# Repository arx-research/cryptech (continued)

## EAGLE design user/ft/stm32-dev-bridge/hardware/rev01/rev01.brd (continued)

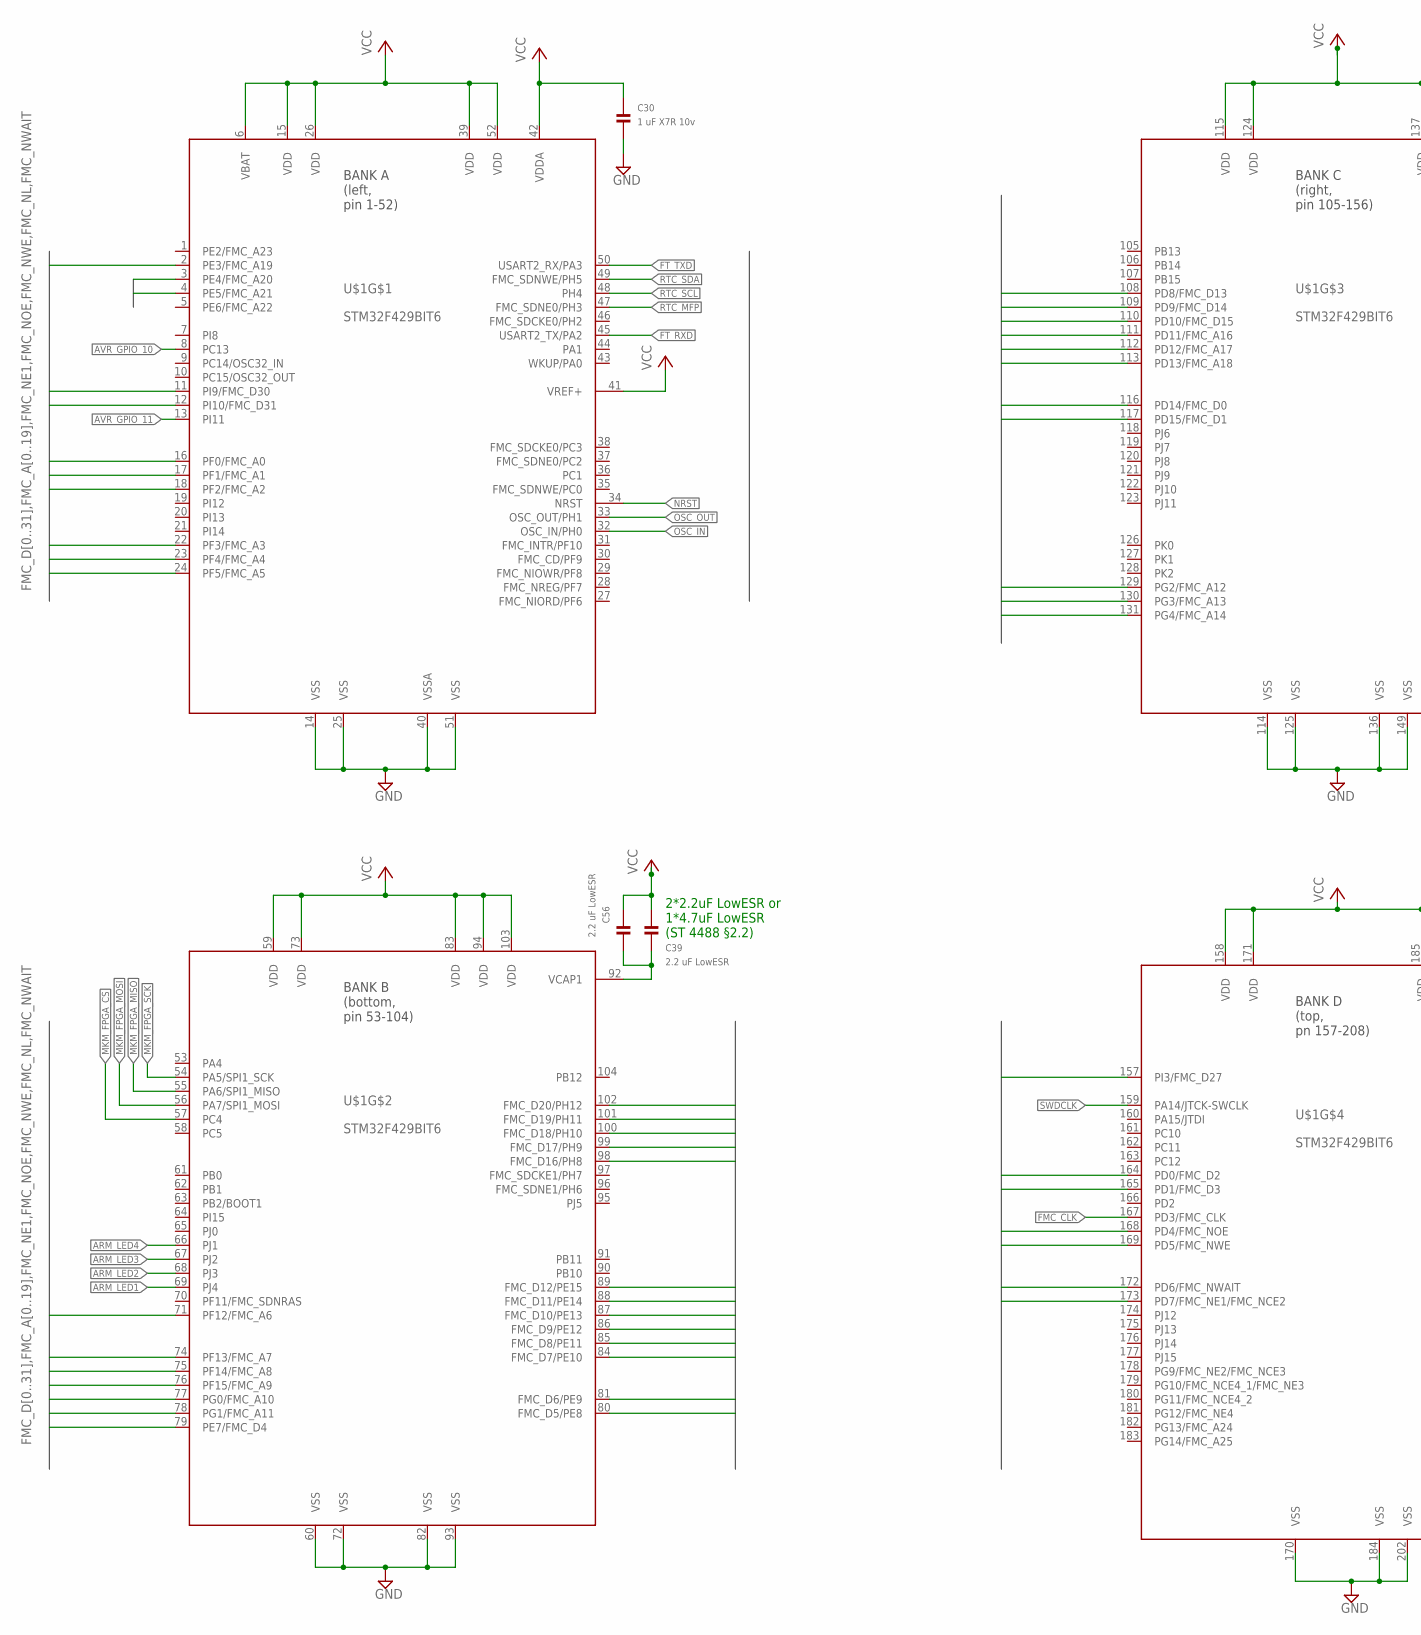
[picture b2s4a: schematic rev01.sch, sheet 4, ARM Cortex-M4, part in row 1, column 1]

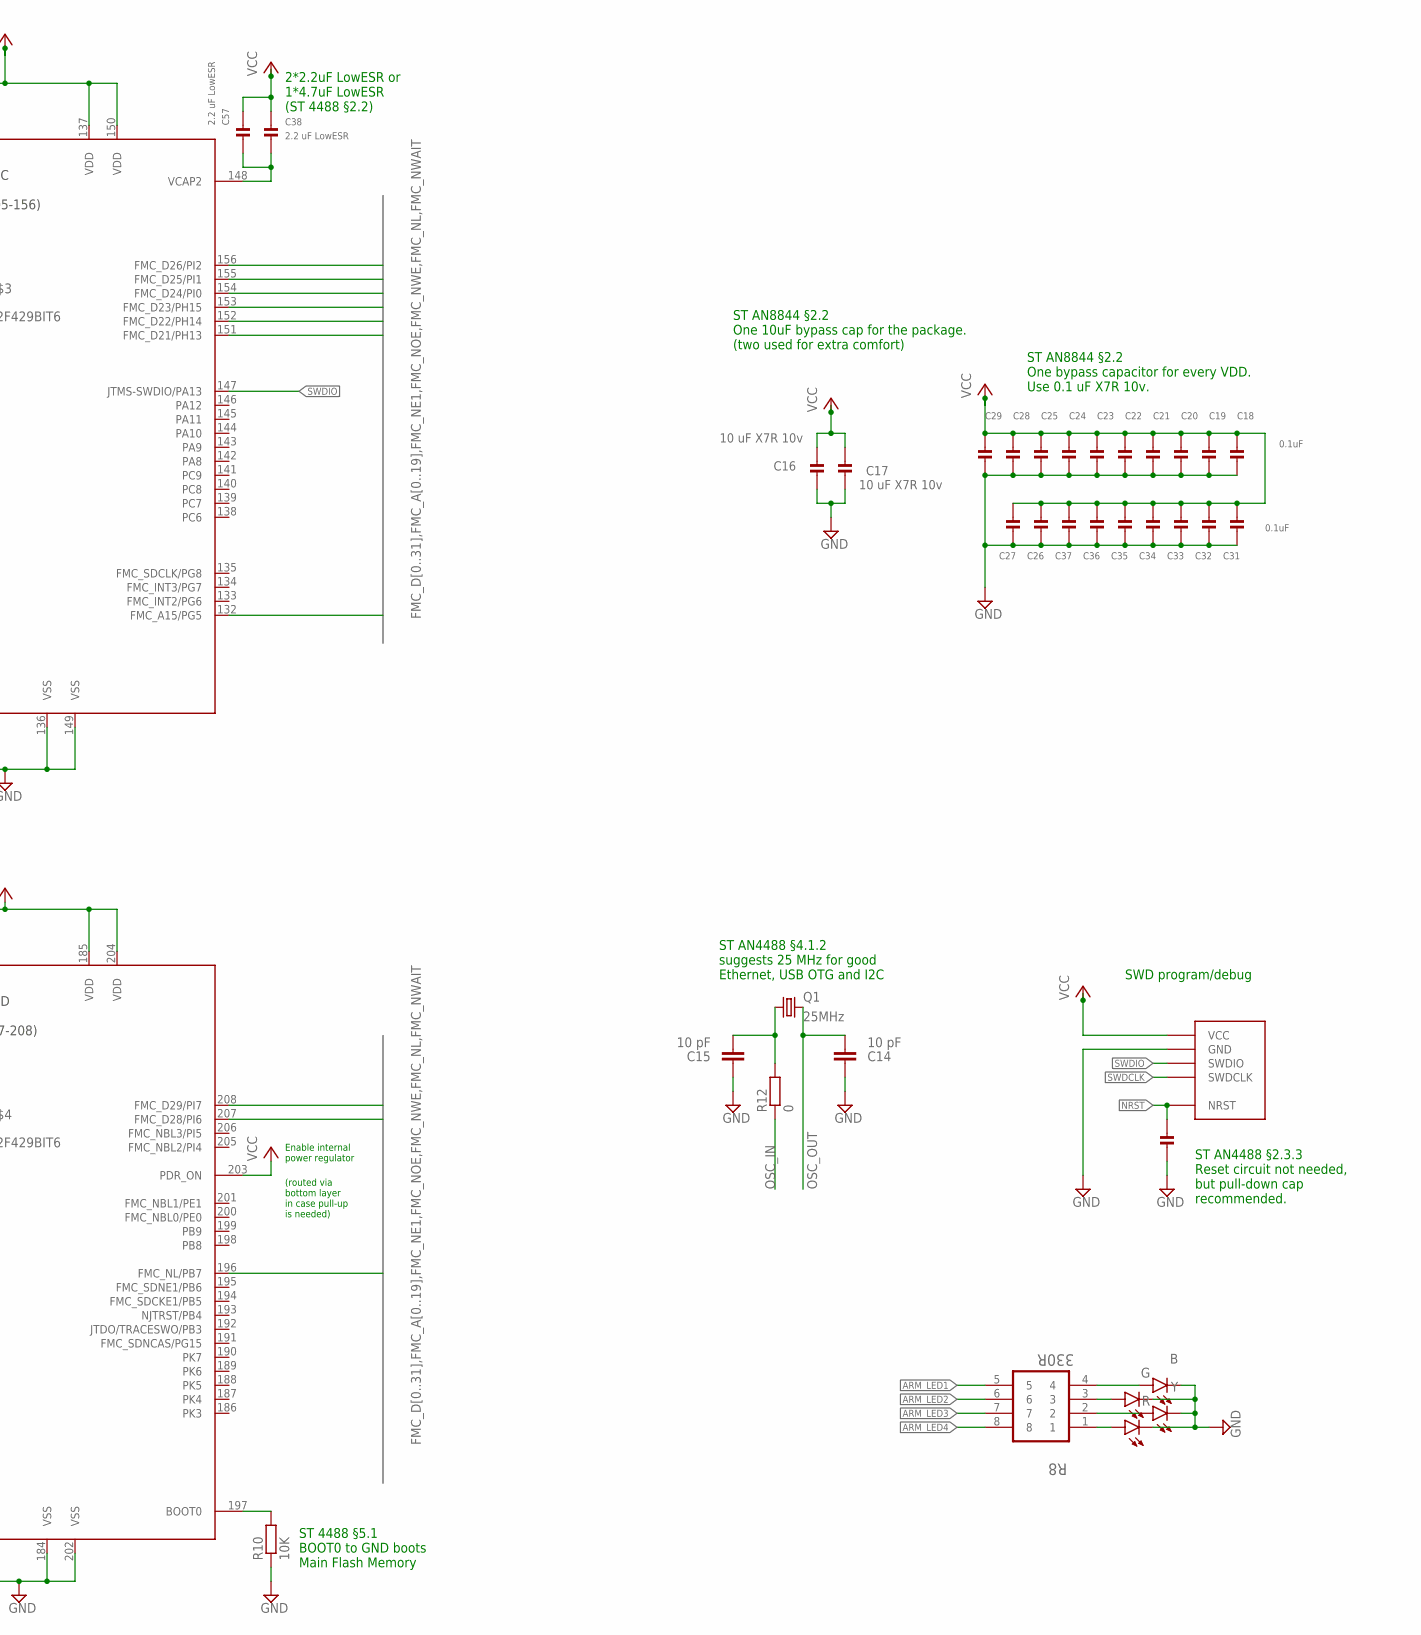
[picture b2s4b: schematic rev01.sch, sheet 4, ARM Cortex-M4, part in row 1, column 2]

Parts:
C14, C15: 10 pF; C0603
C16, C17: 10 uF X7R 10v; 0805
C18, C19, C20, C21, C22, C23, C24, C25, C26, C27, C28, C29, C31, C32, C33, C34, C35, C36, C37, C40: 0.1uF; 0603
C30: 1 uF X7R 10v; 0603
C38, C39, C56, C57: 2.2 uF LowESR; 0603
LED5: B; LED-0603
LED6: G; LED-0603
LED7: Y; LED-0603
LED8: R; LED-0603
Q1: 25MHz; CTS406
R8: 330R; RESCAXE80P320X160X60-8N
R10: 10K; R0603
R12: 0; R0603
U$1: STM32F429BIT6; LQFP-208
U$2: STM32-SWD; 100MIL_THT

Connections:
3V3: C16.1, C17.1, C18.1, C19.1, C20.1, C21.1, C22.1, C23.1, C24.1, C25.1, C26.1, C27.1, C28.1, C29.1, C30.1, C31.1, C32.1, C33.1, C34.1, C35.1, C36.1, C37.1, C38.1, C39.1, C56.1, C57.1, U$1.6 (VBAT), U$1.15 (VDD), U$1.26 (VDD), U$1.39 (VDD), U$1.41 (VREF+), U$1.42 (VDDA), U$1.52 (VDD), U$1.59 (VDD), U$1.73 (VDD), U$1.83 (VDD), U$1.94 (VDD), U$1.103 (VDD), U$1.115 (VDD), U$1.124 (VDD), U$1.137 (VDD), U$1.150 (VDD), U$1.158 (VDD), U$1.171 (VDD), U$1.185 (VDD), U$1.203 (PDR_ON), U$1.204 (VDD), U$2.P$VCC (VCC); also elsewhere on the board
ARM_LED1: R8.5, U$1.69 (PJ4)
ARM_LED2: R8.6, U$1.68 (PJ3)
ARM_LED3: R8.7, U$1.67 (PJ2)
ARM_LED4: R8.8, U$1.66 (PJ1)
AVR_GPIO_10: U$1.8 (PC13); also elsewhere on the board
AVR_GPIO_11: U$1.13 (PI11); also elsewhere on the board
BOOT0: R10.2, U$1.197 (BOOT0)
FMC_A0: U$1.16 (PF0/FMC_A0); also elsewhere on the board
FMC_A1: U$1.17 (PF1/FMC_A1); also elsewhere on the board
FMC_A2: U$1.18 (PF2/FMC_A2); also elsewhere on the board
FMC_A3: U$1.22 (PF3/FMC_A3); also elsewhere on the board
FMC_A4: U$1.23 (PF4/FMC_A4); also elsewhere on the board
FMC_A5: U$1.24 (PF5/FMC_A5); also elsewhere on the board
FMC_A6: U$1.71 (PF12/FMC_A6); also elsewhere on the board
FMC_A7: U$1.74 (PF13/FMC_A7); also elsewhere on the board
FMC_A8: U$1.75 (PF14/FMC_A8); also elsewhere on the board
FMC_A9: U$1.76 (PF15/FMC_A9); also elsewhere on the board
FMC_A10: U$1.77 (PG0/FMC_A10); also elsewhere on the board
FMC_A11: U$1.78 (PG1/FMC_A11); also elsewhere on the board
FMC_A12: U$1.129 (PG2/FMC_A12); also elsewhere on the board
FMC_A13: U$1.130 (PG3/FMC_A13); also elsewhere on the board
FMC_A14: U$1.131 (PG4/FMC_A14); also elsewhere on the board
FMC_A15: U$1.132 (FMC_A15/PG5); also elsewhere on the board
FMC_A16: U$1.111 (PD11/FMC_A16); also elsewhere on the board
FMC_A17: U$1.112 (PD12/FMC_A17); also elsewhere on the board
FMC_A18: U$1.113 (PD13/FMC_A18); also elsewhere on the board
FMC_A19: U$1.2 (PE3/FMC_A19); also elsewhere on the board
FMC_A20: U$1.3 (PE4/FMC_A20); also elsewhere on the board
FMC_A21: U$1.4 (PE5/FMC_A21); also elsewhere on the board
FMC_CLK: U$1.167 (PD3/FMC_CLK); also elsewhere on the board
FMC_D0: U$1.116 (PD14/FMC_D0); also elsewhere on the board
FMC_D1: U$1.117 (PD15/FMC_D1); also elsewhere on the board
FMC_D2: U$1.164 (PD0/FMC_D2); also elsewhere on the board
FMC_D3: U$1.165 (PD1/FMC_D3); also elsewhere on the board
FMC_D4: U$1.79 (PE7/FMC_D4); also elsewhere on the board
FMC_D5: U$1.80 (FMC_D5/PE8); also elsewhere on the board
FMC_D6: U$1.81 (FMC_D6/PE9); also elsewhere on the board
FMC_D7: U$1.84 (FMC_D7/PE10); also elsewhere on the board
FMC_D8: U$1.85 (FMC_D8/PE11); also elsewhere on the board
FMC_D9: U$1.86 (FMC_D9/PE12); also elsewhere on the board
FMC_D10: U$1.87 (FMC_D10/PE13); also elsewhere on the board
FMC_D11: U$1.88 (FMC_D11/PE14); also elsewhere on the board
FMC_D12: U$1.89 (FMC_D12/PE15); also elsewhere on the board
FMC_D13: U$1.108 (PD8/FMC_D13); also elsewhere on the board
FMC_D14: U$1.109 (PD9/FMC_D14); also elsewhere on the board
FMC_D15: U$1.110 (PD10/FMC_D15); also elsewhere on the board
FMC_D16: U$1.98 (FMC_D16/PH8); also elsewhere on the board
FMC_D17: U$1.99 (FMC_D17/PH9); also elsewhere on the board
FMC_D18: U$1.100 (FMC_D18/PH10); also elsewhere on the board
FMC_D19: U$1.101 (FMC_D19/PH11); also elsewhere on the board
FMC_D20: U$1.102 (FMC_D20/PH12); also elsewhere on the board
FMC_D21: U$1.151 (FMC_D21/PH13); also elsewhere on the board
FMC_D22: U$1.152 (FMC_D22/PH14); also elsewhere on the board
FMC_D23: U$1.153 (FMC_D23/PH15); also elsewhere on the board
FMC_D24: U$1.154 (FMC_D24/PI0); also elsewhere on the board
FMC_D25: U$1.155 (FMC_D25/PI1); also elsewhere on the board
FMC_D26: U$1.156 (FMC_D26/PI2); also elsewhere on the board
FMC_D27: U$1.157 (PI3/FMC_D27); also elsewhere on the board
FMC_D28: U$1.207 (FMC_D28/PI6); also elsewhere on the board
FMC_D29: U$1.208 (FMC_D29/PI7); also elsewhere on the board
FMC_D30: U$1.11 (PI9/FMC_D30); also elsewhere on the board
FMC_D31: U$1.12 (PI10/FMC_D31); also elsewhere on the board
FMC_NE1: U$1.173 (PD7/FMC_NE1/FMC_NCE2); also elsewhere on the board
FMC_NL: U$1.196 (FMC_NL/PB7); also elsewhere on the board
FMC_NOE: U$1.168 (PD4/FMC_NOE); also elsewhere on the board
FMC_NWAIT: U$1.172 (PD6/FMC_NWAIT); also elsewhere on the board
FMC_NWE: U$1.169 (PD5/FMC_NWE); also elsewhere on the board
FT_RXD: U$1.45 (USART2_TX/PA2); also elsewhere on the board
FT_TXD: U$1.50 (USART2_RX/PA3); also elsewhere on the board
GND: C14.1, C15.1, C16.2, C17.2, C18.2, C19.2, C20.2, C21.2, C22.2, C23.2, C24.2, C25.2, C26.2, C27.2, C28.2, C29.2, C30.2, C31.2, C32.2, C33.2, C34.2, C35.2, C36.2, C37.2, C40.2, LED5.C, LED6.C, LED7.C, LED8.C, R10.1, U$1.14 (VSS), U$1.25 (VSS), U$1.40 (VSSA), U$1.51 (VSS), U$1.60 (VSS), U$1.72 (VSS), U$1.82 (VSS), U$1.93 (VSS), U$1.114 (VSS), U$1.125 (VSS), U$1.136 (VSS), U$1.149 (VSS), U$1.170 (VSS), U$1.184 (VSS), U$1.202 (VSS), U$2.P$GND (GND); also elsewhere on the board
MKM_FPGA_CS: U$1.57 (PC4); also elsewhere on the board
MKM_FPGA_MISO: U$1.55 (PA6/SPI1_MISO); also elsewhere on the board
MKM_FPGA_MOSI: U$1.56 (PA7/SPI1_MOSI); also elsewhere on the board
MKM_FPGA_SCK: U$1.54 (PA5/SPI1_SCK); also elsewhere on the board
unnamed: LED5.A, R8.4
unnamed: LED6.A, R8.3
unnamed: LED7.A, R8.2
unnamed: LED8.A, R8.1
unnamed: C15.2, Q1.1, R12.2
NRST: C40.1, U$1.34 (NRST), U$2.P$NRST (NRST)
OSC_IN: R12.1, U$1.32 (OSC_IN/PH0)
OSC_OUT: C14.2, Q1.3 (2), U$1.33 (OSC_OUT/PH1)
RTC_MFP: U$1.47 (FMC_SDNE0/PH3); also elsewhere on the board
RTC_SCL: U$1.48 (PH4); also elsewhere on the board
RTC_SDA: U$1.49 (FMC_SDNWE/PH5); also elsewhere on the board
SWDCLK: U$1.159 (PA14/JTCK-SWCLK), U$2.P$SWDCLK (SWDCLK)
SWDIO: U$1.147 (JTMS-SWDIO/PA13), U$2.P$SWDIO (SWDIO)
VCAP1: C39.2, C56.2, U$1.92 (VCAP1)
VCAP2: C38.2, C57.2, U$1.148 (VCAP2)

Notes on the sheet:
ST AN8844 §2.2 One bypass capacitor for every VDD. Use 0.1 uF X7R 10v.
ST AN8844 §2.2 One 10uF bypass cap for the package. (two used for extra comfort)
2*2.2uF LowESR or 1*4.7uF LowESR (ST 4488 §2.2)
ST 4488 §5.1 BOOT0 to GND boots Main Flash Memory
ST AN4488 §4.1.2 suggests 25 MHz for good Ethernet, USB OTG and I2C
SWD program/debug
ST AN4488 §2.3.3 Reset circuit not needed, but pull-down cap recommended.
Enable internal power regulator
(routed via bottom layer in case pull-up is needed)

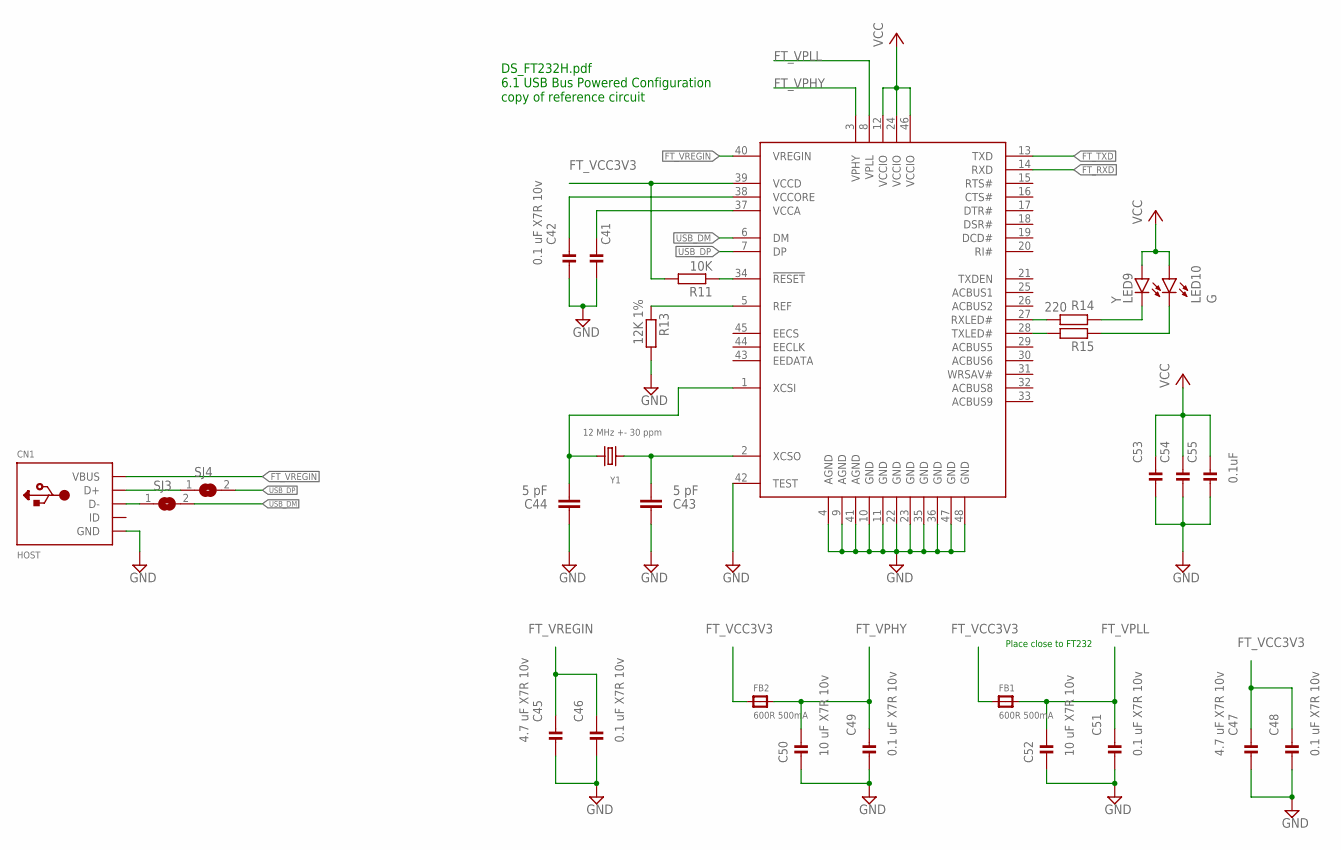
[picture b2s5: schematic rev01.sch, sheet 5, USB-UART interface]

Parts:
C41, C42, C46, C48, C49, C51: 0.1 uF X7R 10v; 0603
C43, C44: 5 pF; C0603
C45, C47: 4.7 uF X7R 10v; 0603
C50, C52: 10 uF X7R 10v; _0805
C53, C54, C55: 0.1uF; 0603
CN1: HOST; USB-MINIB
FB1, FB2: 600R 500mA; _0603MP
LED9: Y; LED-0603
LED10: G; LED-0603
R11: 10K; R0603
R13: 12K 1%; R0603
R14, R15: 220; R0603
SJ3, SJ4: SOLDERJUMPERCLOSED; SOLDERJUMPER_CLOSEDWIRE
U$3: FT232H_SERIAL; FT2323HL_LQFP48
Y1: 12 MHz +- 30 ppm; CRYSTAL_3.2X2.5

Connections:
FT_REF: R13.1, U$3.5 (REF)
FT_RESET: R11.1, U$3.34 (!RESET)
FT_RXD: U$3.14 (RXD); also elsewhere on the board
FT_RXLED: R14.2, U$3.27 (RXLED#)
FT_TXD: U$3.13 (TXD); also elsewhere on the board
FT_TXLED: R15.2, U$3.28 (TXLED#)
FT_VCC3V3: C47.1, C48.1, C53.1, C54.1, C55.1, FB1.1, FB2.1, LED9.A, LED10.A, R11.2, U$3.12 (VCCIO), U$3.24 (VCCIO), U$3.39 (VCCD), U$3.46 (VCCIO)
FT_VCCA: C41.1, U$3.37 (VCCA)
FT_VCCORE: C42.1, U$3.38 (VCCORE)
FT_VPHY: C49.1, C50.1, FB2.2, U$3.3 (VPHY)
FT_VPLL: C51.1, C52.1, FB1.2, U$3.8 (VPLL)
FT_VREGIN: C45.1, C46.1, CN1.VBUS, U$3.40 (VREGIN)
GND: C41.2, C42.2, C43.1, C44.1, C45.2, C46.2, C47.2, C48.2, C49.2, C50.2, C51.2, C52.2, C53.2, C54.2, C55.2, CN1.GND, R13.2, U$3.4 (AGND), U$3.9 (AGND), U$3.10 (GND), U$3.11 (GND), U$3.22 (GND), U$3.23 (GND), U$3.35 (GND), U$3.36 (GND), U$3.41 (AGND), U$3.42 (TEST), U$3.47 (GND), U$3.48 (GND); also elsewhere on the board
unnamed: C44.2, U$3.1 (XCSI), Y1.1
unnamed: C43.2, U$3.2 (XCSO), Y1.2
unnamed: LED9.C, R14.1
unnamed: LED10.C, R15.1
USBDM: CN1.D-, SJ3.1
USBDP: CN1.D+, SJ4.1
USB_DM: SJ3.2, U$3.6 (DM)
USB_DP: SJ4.2, U$3.7 (DP)

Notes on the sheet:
DS_FT232H.pdf 6.1 USB Bus Powered Configuration copy of reference circuit
Place close to FT232

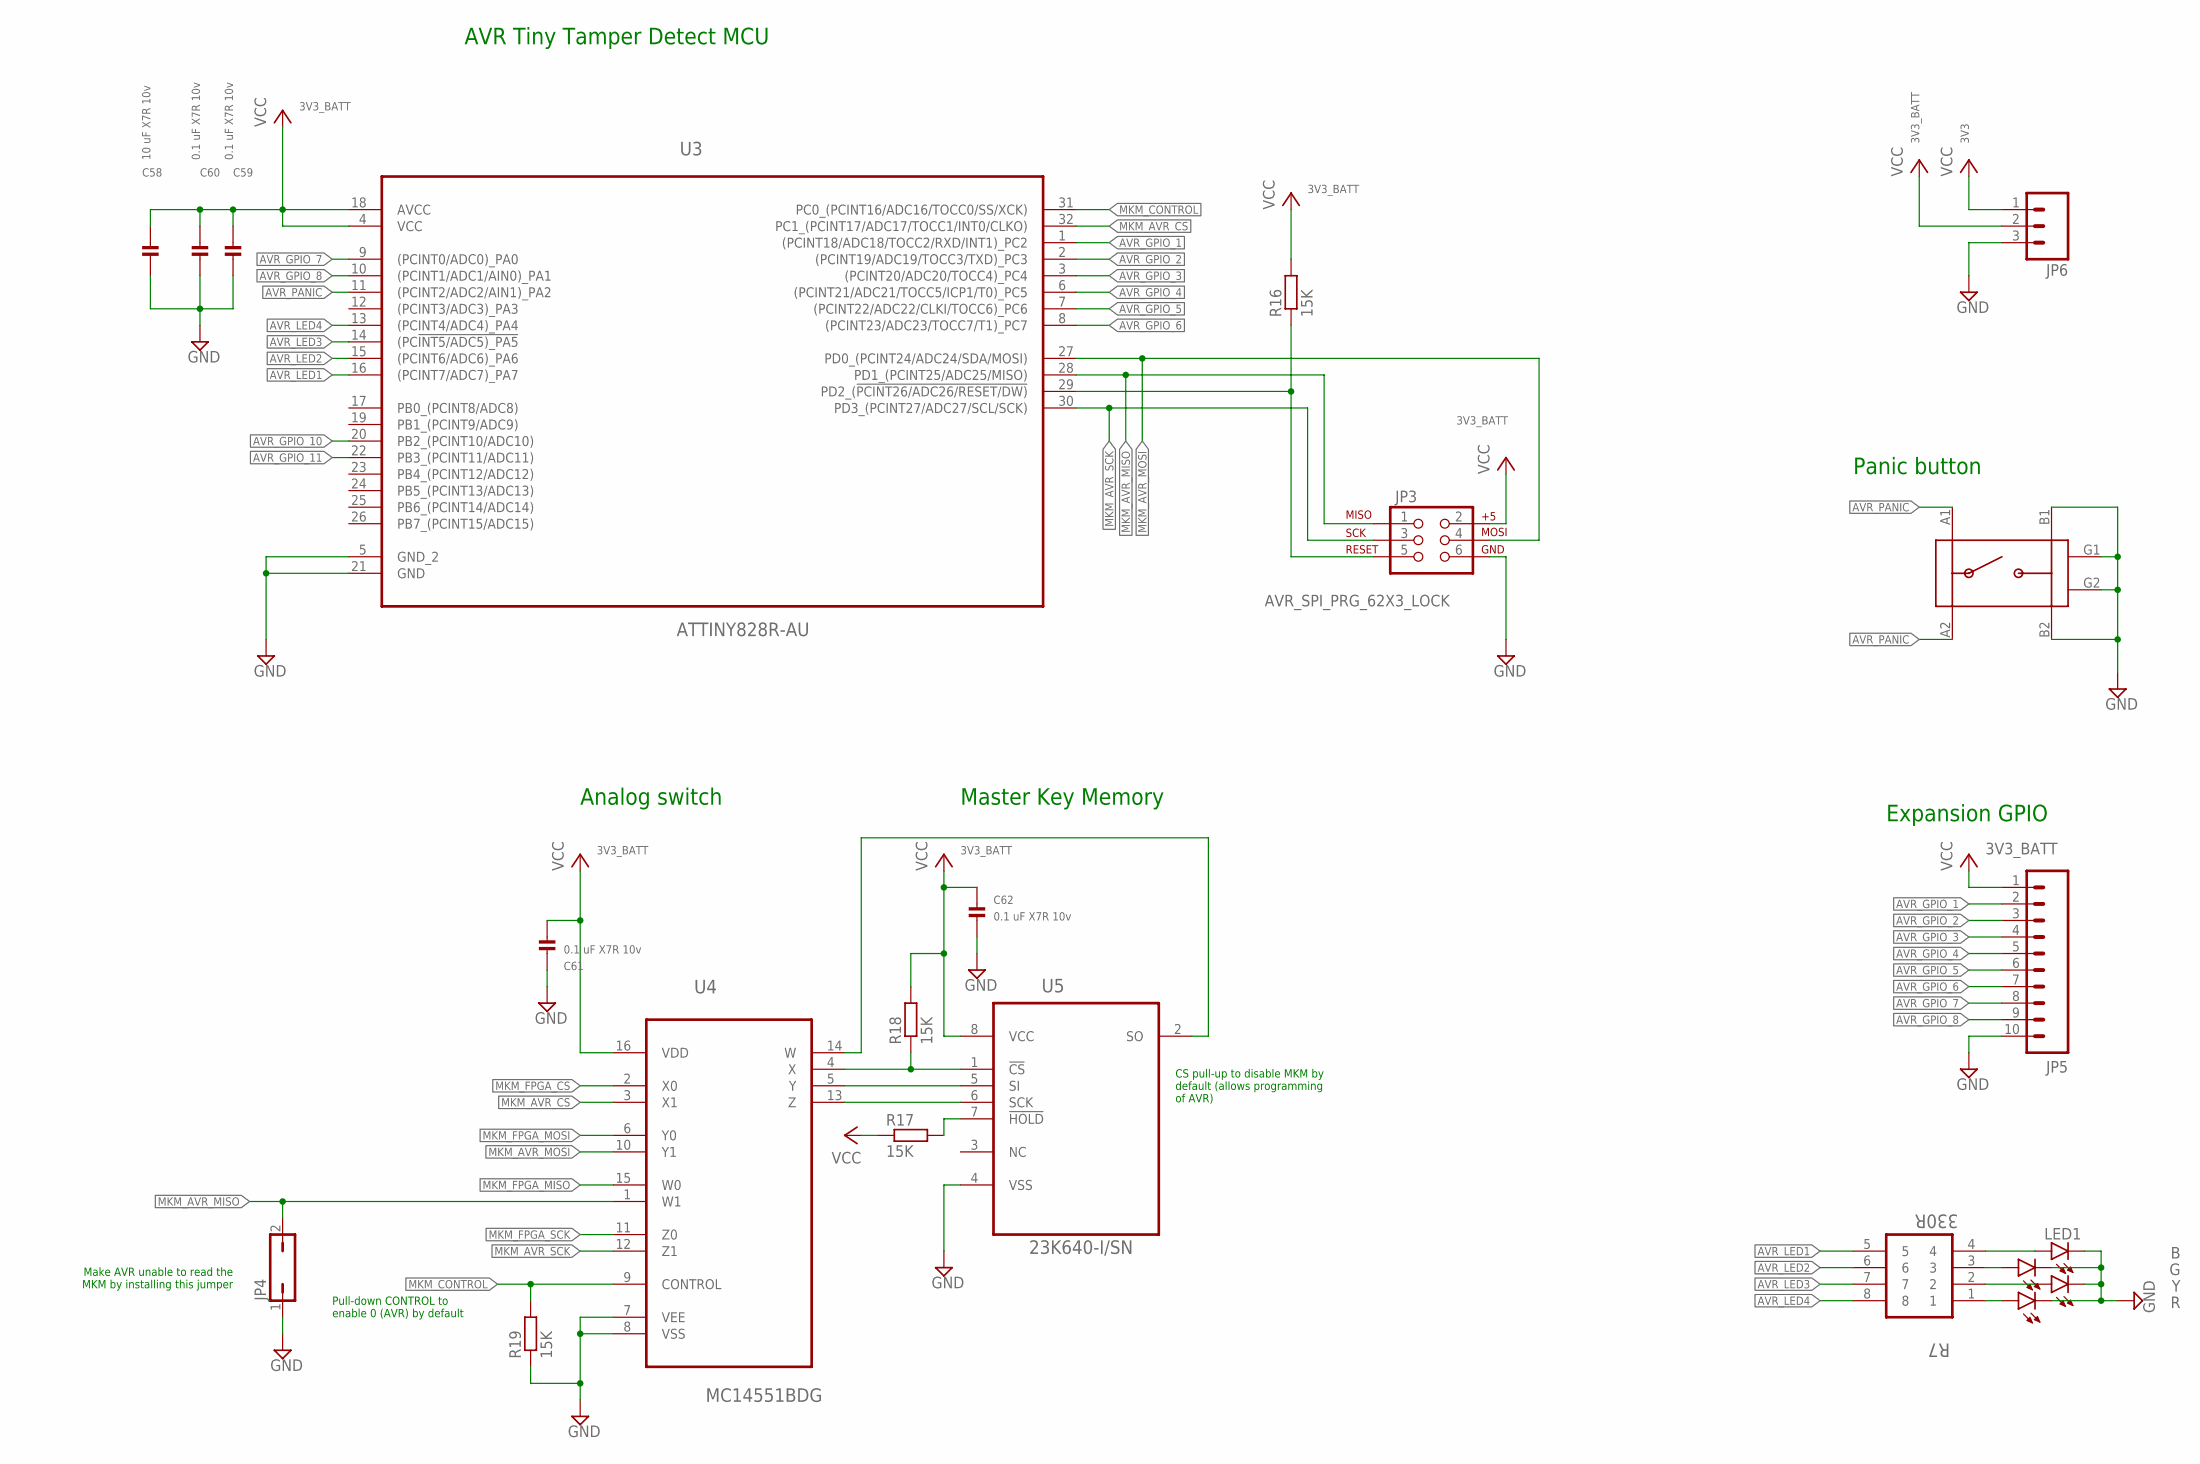
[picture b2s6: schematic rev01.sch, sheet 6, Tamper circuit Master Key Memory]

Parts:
C58: 10 uF X7R 10v; 0805
C59, C60, C61, C62: 0.1 uF X7R 10v; 0603
JP3: AVR_SPI_PRG_62X3_LOCK; 2X3_LOCK
JP4: JP1Q; JP1
JP5: M10LOCK; 1X10_LOCK
JP6: M03LOCK; 1X03_LOCK
LED1: B; LED-0603
LED2: G; LED-0603
LED3: Y; LED-0603
LED4: R; LED-0603
R7: 330R; RESCAXE80P320X160X60-8N
R16, R17, R18, R19: 15K; R0603
U3: ATTINY828R-AU; QFP80P900X900X120-32N
U4: MC14551BDG; SOIC127P600X175-16N
U5: 23K640-I/SN; SOIC127P600X175-8N
U$4: TACTILE_SWITCH

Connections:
3V3: JP6.1; also elsewhere on the board
3V3_BATT: C58.1, C59.1, C60.1, C61.1, C62.1, JP3.2, JP5.1, JP6.2, R16.2, R17.1, R18.2, U3.4 (VCC), U3.18 (AVCC), U4.16 (VDD), U5.8 (VCC); also elsewhere on the board
!MKM_CS: R18.1, U4.4 (X), U5.1 (!CS)
AVR_GPIO_1: JP5.2, U3.1 ((PCINT18/ADC18/TOCC2/RXD/INT1)_PC2)
AVR_GPIO_2: JP5.3, U3.2 ((PCINT19/ADC19/TOCC3/TXD)_PC3)
AVR_GPIO_3: JP5.4, U3.3 ((PCINT20/ADC20/TOCC4)_PC4)
AVR_GPIO_4: JP5.5, U3.6 ((PCINT21/ADC21/TOCC5/ICP1/T0)_PC5)
AVR_GPIO_5: JP5.6, U3.7 ((PCINT22/ADC22/CLKI/TOCC6)_PC6)
AVR_GPIO_6: JP5.7, U3.8 ((PCINT23/ADC23/TOCC7/T1)_PC7)
AVR_GPIO_7: JP5.8, U3.9 ((PCINT0/ADC0)_PA0)
AVR_GPIO_8: JP5.9, U3.10 ((PCINT1/ADC1/AIN0)_PA1)
AVR_GPIO_10: U3.20 (PB2_(PCINT10/ADC10)); also elsewhere on the board
AVR_GPIO_11: U3.22 (PB3_(PCINT11/ADC11)); also elsewhere on the board
AVR_LED1: R7.5, U3.16 ((PCINT7/ADC7)_PA7)
AVR_LED2: R7.6, U3.15 ((PCINT6/ADC6)_PA6)
AVR_LED3: R7.7, U3.14 ((PC!INT5/ADC5)_PA5)
AVR_LED4: R7.8, U3.13 ((PCINT4/ADC4)_PA4)
AVR_PANIC: U3.11 ((PCINT2/ADC2/AIN1)_PA2), U$4.A1, U$4.A2
AVR_RESET: JP3.5, R16.1, U3.29 (PD2_(!PCINT26/ADC26/RESET/DW))
GND: C58.2, C59.2, C60.2, C61.2, C62.2, JP3.6, JP4.1, JP5.10, JP6.3, LED1.C, LED2.C, LED3.C, LED4.C, R19.1, U3.5 (GND_2), U3.21 (GND), U4.7 (VEE), U4.8 (VSS), U5.4 (VSS), U$4.B1, U$4.B2, U$4.G1, U$4.G2; also elsewhere on the board
MKM_AVR_CS: U3.32 (PC1_(PCINT17/ADC17/TOCC1/INT0/CLKO)), U4.3 (X1)
MKM_AVR_MISO: JP3.1, JP4.2, U3.28 (PD1_(PCINT25/ADC25/MISO)), U4.1 (W1)
MKM_AVR_MOSI: JP3.4, U3.27 (PD0_(PCINT24/ADC24/SDA/MOSI)), U4.10 (Y1)
MKM_AVR_SCK: JP3.3, U3.30 (PD3_(PCINT27/ADC27/SCL/SCK)), U4.12 (Z1)
MKM_CONTROL: R19.2, U3.31 (PC0_(PCINT16/ADC16/TOCC0/SS/XCK)), U4.9 (CONTROL)
MKM_FPGA_CS: U4.2 (X0); also elsewhere on the board
MKM_FPGA_MISO: U4.15 (W0); also elsewhere on the board
MKM_FPGA_MOSI: U4.6 (Y0); also elsewhere on the board
MKM_FPGA_SCK: U4.11 (Z0); also elsewhere on the board
MKM_MISO: U4.14 (W), U5.2 (SO)
MKM_MOSI: U4.5 (Y), U5.5 (SI)
MKM_SCK: U4.13 (Z), U5.6 (SCK)
unnamed: LED1.A, R7.4
unnamed: LED2.A, R7.3
unnamed: LED3.A, R7.2
unnamed: LED4.A, R7.1
unnamed: R17.2, U5.7 (!HOLD)

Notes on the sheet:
CS pull-up to disable MKM by default (allows programming of AVR)
Pull-down CONTROL to enable 0 (AVR) by default
Master Key Memory
Analog switch
AVR Tiny Tamper Detect MCU
Make AVR unable to read the MKM by installing this jumper
Panic button
Expansion GPIO

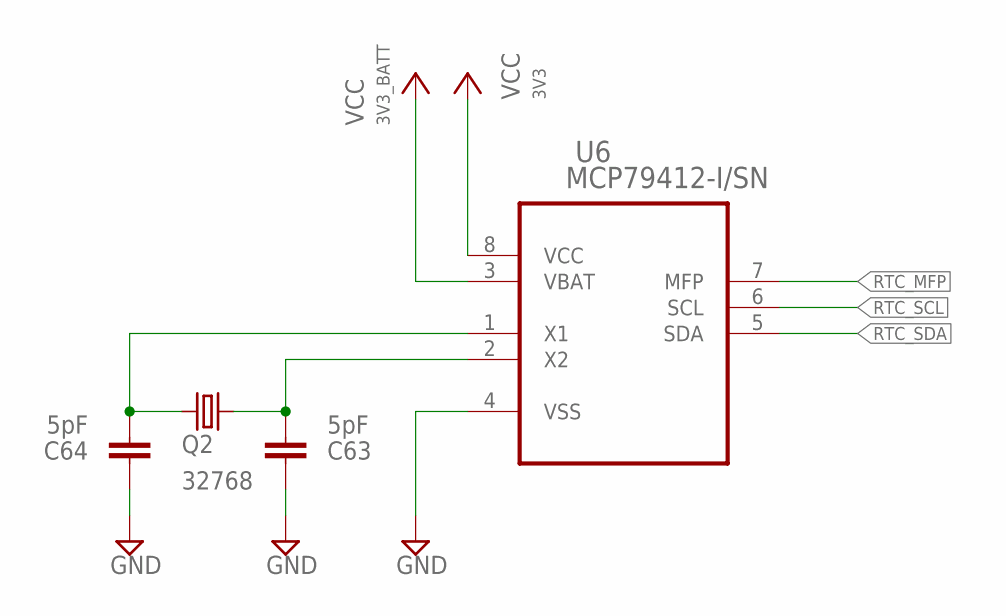
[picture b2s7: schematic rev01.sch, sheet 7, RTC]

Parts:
C63, C64: 5pF; C0603
Q2: 32768; TC26H
U6: MCP79412-I/SN; SOIC127P600X175-8N

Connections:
3V3: U6.8 (VCC); also elsewhere on the board
3V3_BATT: U6.3 (VBAT); also elsewhere on the board
GND: C63.1, C64.1, U6.4 (VSS); also elsewhere on the board
RTC_MFP: U6.7 (MFP); also elsewhere on the board
RTC_SCL: U6.6 (SCL); also elsewhere on the board
RTC_SDA: U6.5 (SDA); also elsewhere on the board
RTC_X1: C64.2, Q2.1, U6.1 (X1)
RTC_X2: C63.2, Q2.2, U6.2 (X2)

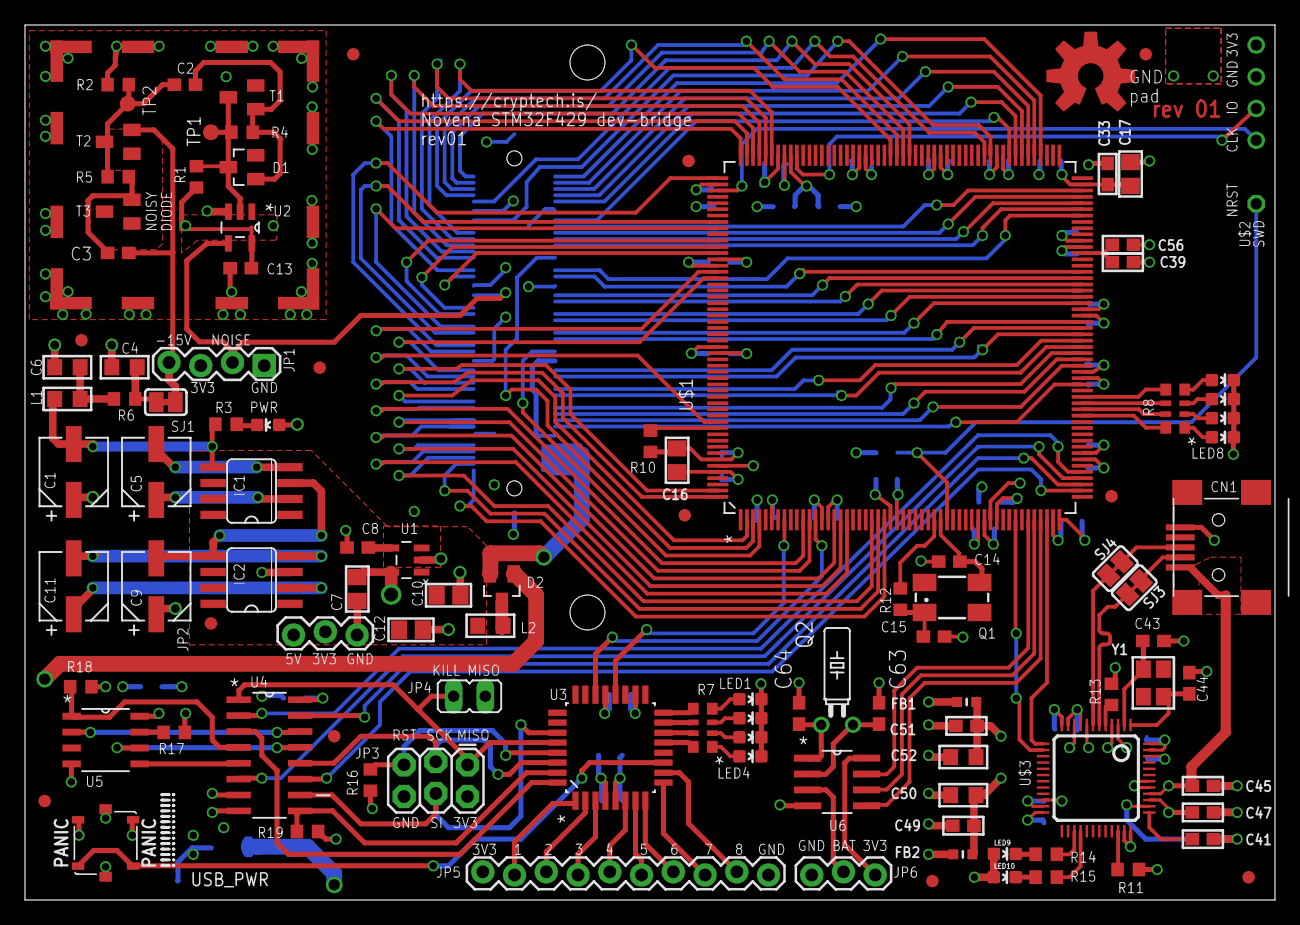
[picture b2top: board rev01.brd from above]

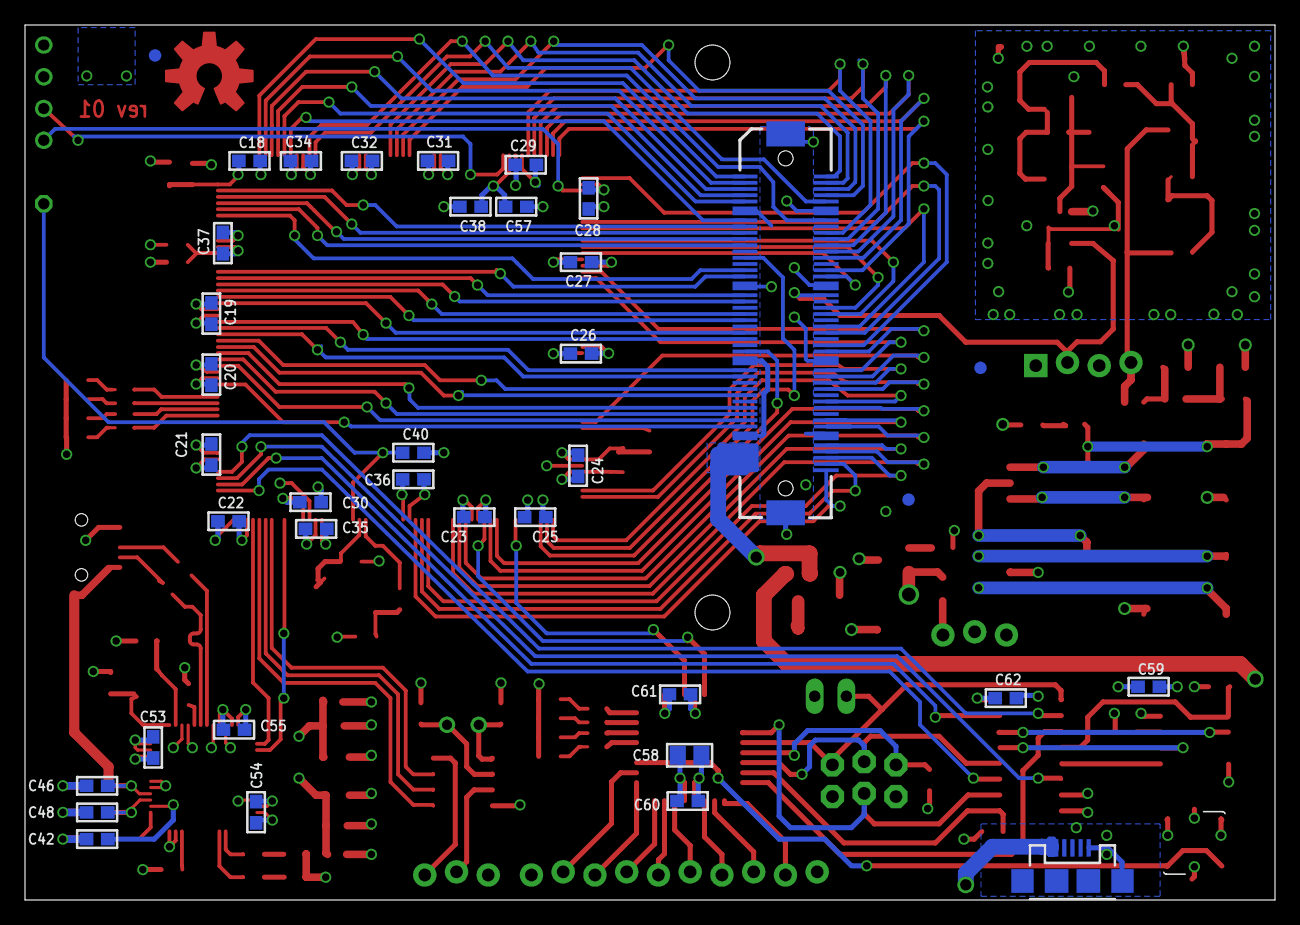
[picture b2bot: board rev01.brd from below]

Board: 4 copper layers, 100.0 x 70.0 mm, 148 parts (37 on the bottom side), 161 nets.
